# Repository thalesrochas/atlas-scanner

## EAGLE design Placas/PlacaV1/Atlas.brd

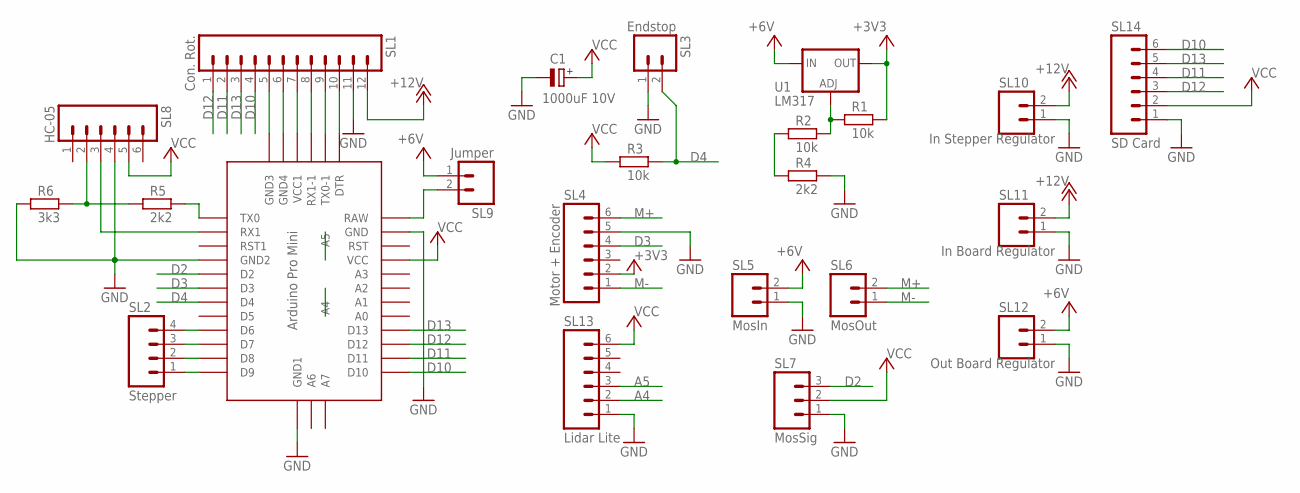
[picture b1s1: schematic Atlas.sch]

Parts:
C1: 1000uF 10V; E5-10,5
R1, R2, R3: 10k; 0207/10
R4, R5: 2k2; 0207/10
R6: 3k3; 0207/10
SL1: Con. Rot.; 12P
SL2: Stepper; 04P
SL3: Endstop; 02P
SL4: Motor + Encoder; 06P
SL5: MosIn; 02P
SL6: MosOut; 02P
SL7: MosSig; 03P
SL8: HC-05; 06P
SL9: Jumper; 02P
SL10: In Stepper Regulator; 02P
SL11: In Board Regulator; 02P
SL12: Out Board Regulator; 02P
SL13: Lidar Lite; 06P
SL14: SD Card; 06P
U1: LM317; TO220-ADJ
U$1: ABK-PRO-MINI

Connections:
+3V3: R1.2, SL4.2, U1.OUT
+6V: SL5.2, SL9.1, SL12.2, U1.IN
+12V: SL1.12, SL10.2, SL11.2
A4: SL13.2, U$1.A4
A5: SL13.3, U$1.A5
D2: SL7.3, U$1.D2
D3: SL4.4, U$1.D3
D4: R3.2, SL3.2, U$1.D4
D10: SL1.4, SL14.6, U$1.D10
D11: SL1.2, SL14.4, U$1.D11
D12: SL1.1, SL14.3, U$1.D12
D13: SL1.3, SL14.5, U$1.D13
DTR: SL1.10, U$1.DTR
GND: C1.-, R4.2, R6.1, SL1.5, SL1.6, SL1.11, SL3.1, SL4.5, SL5.1, SL7.1, SL8.4, SL10.1, SL11.1, SL12.1, SL13.1, SL14.1, U$1.GND, U$1.GND1 (GND2), U$1.GND2 (GND3), U$1.GND3 (GND4), U$1.GND4 (GND1)
M+: SL4.6, SL6.2
M-: SL4.1, SL6.1
unnamed: R5.2, U$1.TX0
unnamed: SL9.2, U$1.RAW
unnamed: R2.1, R4.1
unnamed: R5.1, R6.2, SL8.2
unnamed: R1.1, R2.2, U1.ADJ
unnamed: SL8.3, U$1.RX1
unnamed: SL2.1, U$1.D9
unnamed: SL2.2, U$1.D8
unnamed: SL2.3, U$1.D7
unnamed: SL2.4, U$1.D6
RX1: SL1.8, U$1.RX1-1
TX0: SL1.9, U$1.TX0-1
VCC: C1.+, R3.1, SL1.7, SL7.2, SL8.5, SL13.6, SL14.2, U$1.VCC, U$1.VCC1

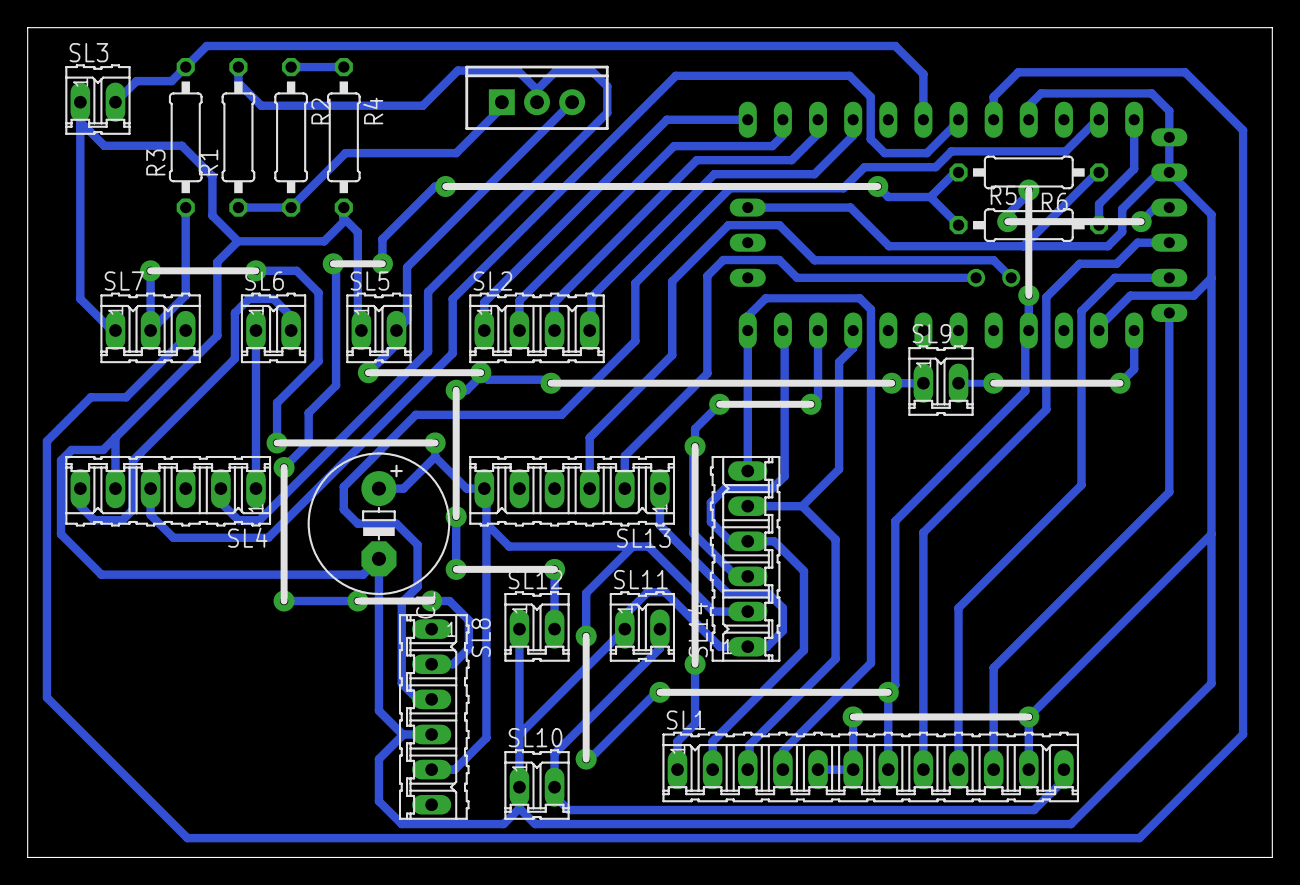
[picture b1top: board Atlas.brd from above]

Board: 2 copper layers, 90.0 x 60.0 mm, 23 parts (0 on the bottom side), 29 nets.

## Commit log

2018-01-05 Adicionado arquivo de testes
2018-07-30 Adicionado arquivo de código principal Atlas.ino.
2018-07-30 Adicionada ação inicial do motor de passo.
2018-07-30 Adicionada integração com o sensor LIDAR. Testes com medição simples de distância.
2018-07-31 Fix na Documentação
2018-08-02 Adicionado comentários, constantes, logs e acesso log de captura em cartão de memória
2018-08-02 Adicionado motor com encoder. Interrupção do encoder configurada. Armazenamento de coordenadas no cartão.
2018-08-02 Fix em nome de variável.
2018-08-02 Ajustes nas capturas de pontos. Ajustes em cálculos de variáveis.
2018-08-09 Fix em escrita no arquivo
2018-08-09 Adicionado README
2018-08-23 Adicionado movimento no sentido de Phi + cálculo da posição em Phi.
2018-08-23 Adicionados todos os arquivos de testes realizados até o momento.
2018-08-23 Scripts de testes de gráfico em Matlab
2018-11-16 Adicionados arquivos de teste
2018-11-16 Adicionada documentação
2018-11-16 Adicionada Placa Versão 1
2019-03-19 Remoção de arquivos desnecessários
2019-03-19 Adicionada documentação geral
2019-03-19 Cronograma
2019-03-19 Atualização de placas
2019-03-19 Adicionadas peças
2019-11-07 Adicionados diversos arquivos de teste
2019-11-07 Adicionada correção de giro que causava desalinhamento das voltas
2019-11-09 Ajustes no cálculo do acumulador
2019-11-09 Adicionados novos arquivos de teste
2019-11-14 Ajustes no código e novos arquivos de teste
2019-11-21 Adicionados resultados que serão usados no TCC
2019-11-21 Código Final

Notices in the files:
parts and their libraries:
SparkFun-IC-Power: Licensing: Creative Commons ShareAlike 4.0 International - https://creativecommons.org/licenses/by-sa/4.0
